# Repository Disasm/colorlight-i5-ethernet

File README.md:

# `colorlight-i5-ethernet`

Dual gigabit Ethernet interface board for [Colorlight i5 Extension Board](https://github.com/wuxx/Colorlight-FPGA-Projects). 

This board is based on [i5ether](https://github.com/kazkojima/colorlight-i5-tips/) project by
[@kazkojima](https://github.com/kazkojima).

Manufactured on JLCPCB (see `gerbers` directory). Tested with the [colorlight_i5.py example](https://github.com/litex-hub/litex-boards/blob/master/litex_boards/targets/colorlight_i5.py)
from LiteX.

# Bill of Materials

| Item                        | Part #               | LCSC Part # | Qty |
|-----------------------------|----------------------|-------------|-----|
| Connector (J1)              | X6521WR-2x15H-C30D60 | [C725927]   | 1   |
| Ethernet connector (J2, J3) | 48F-01GY2DPL2NL      | [C123172]   | 2   |
| Capacitor (C1, C2)          | GRM319R71H104KA01D   | [C86047]    | 2   |
| Capacitor (C3)              | 1812B472K202CT       | [C304036]   | 1   |

[C123172]: https://lcsc.com/product-detail/Ethernet-Connectors-Modular-Connectors-RJ45-RJ11_Shanghai-YDS-Tech-48F-01GY2DPL2NL_C123172.html
[C86047]: https://lcsc.com/product-detail/Multilayer-Ceramic-Capacitors-MLCC-SMD-SMT_Murata-Electronics-GRM319R71H104KA01D_C86047.html
[C304036]: https://lcsc.com/product-detail/Multilayer-Ceramic-Capacitors-MLCC-SMD-SMT_Walsin-Tech-Corp-1812B472K202CT_C304036.html
[C725927]: https://lcsc.com/product-detail/Pin-Headers_XKB-Connectivity-X6521WR-2x15H-C30D60_C725927.html

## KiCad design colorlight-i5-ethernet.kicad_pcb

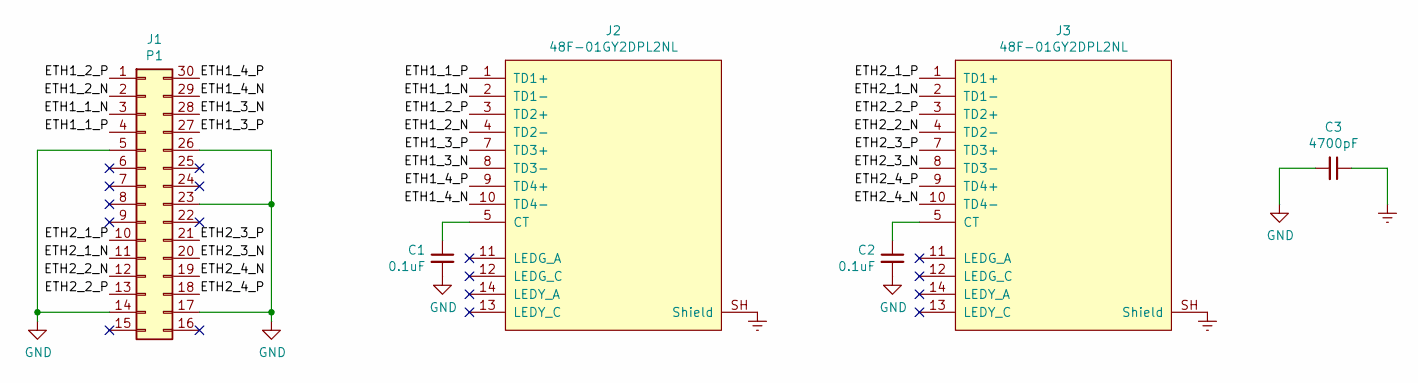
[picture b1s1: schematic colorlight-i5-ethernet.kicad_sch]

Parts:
C1, C2: 0.1uF; C_1206_3216Metric
C3: 4700pF; C_1812_4532Metric; MFR.Part # 1812B472K202CT; LCSC Part # C304036
J1: P1; PinHeader_2x15_P2.54mm_Horizontal_PMOD
J2, J3: 48F-01GY2DPL2NL; LCSC Part # C123172

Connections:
/ETH1_1_N: J1.3, J2.2 (TD1-)
/ETH1_1_P: J1.4, J2.1 (TD1+)
/ETH1_2_N: J1.2, J2.4 (TD2-)
/ETH1_2_P: J1.1, J2.3 (TD2+)
/ETH1_3_N: J1.28, J2.8 (TD3-)
/ETH1_3_P: J1.27, J2.7 (TD3+)
/ETH1_4_N: J1.29, J2.10 (TD4-)
/ETH1_4_P: J1.30, J2.9 (TD4+)
/ETH2_1_N: J1.11, J3.2 (TD1-)
/ETH2_1_P: J1.10, J3.1 (TD1+)
/ETH2_2_N: J1.12, J3.4 (TD2-)
/ETH2_2_P: J1.13, J3.3 (TD2+)
/ETH2_3_N: J1.20, J3.8 (TD3-)
/ETH2_3_P: J1.21, J3.7 (TD3+)
/ETH2_4_N: J1.19, J3.10 (TD4-)
/ETH2_4_P: J1.18, J3.9 (TD4+)
Earth: C3.1, J2.SH (Shield), J3.SH (Shield)
GND: C1.2, C2.2, C3.2, J1.5, J1.14, J1.17, J1.23, J1.26
unnamed: C1.1, J2.5 (CT), J2.6 (CT)
unnamed: C2.1, J3.5 (CT), J3.6 (CT)

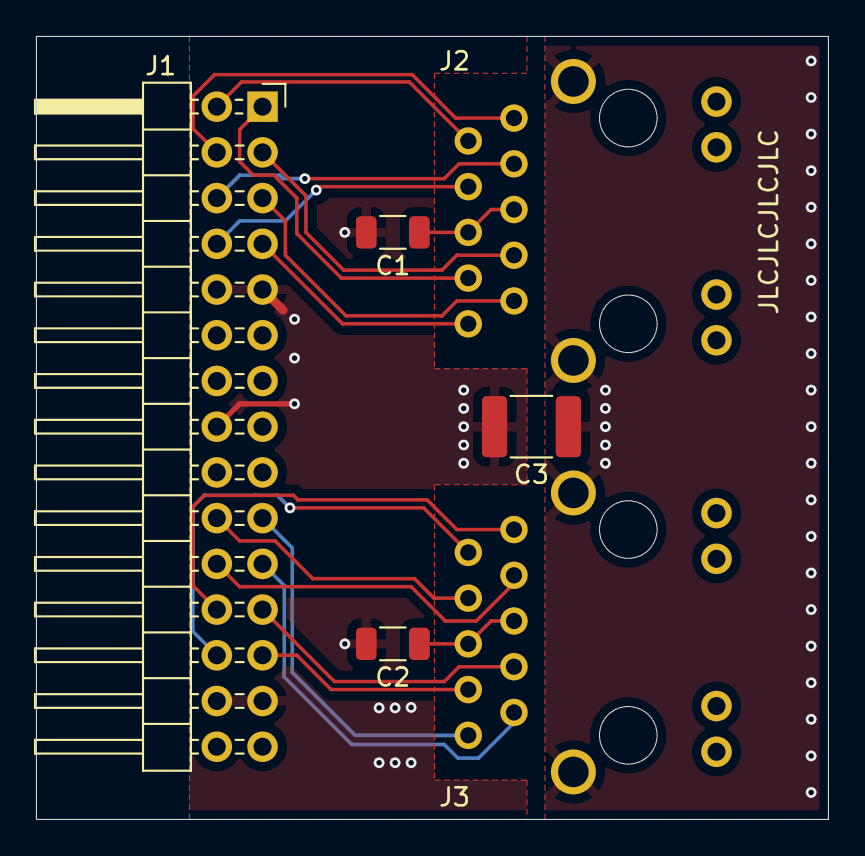
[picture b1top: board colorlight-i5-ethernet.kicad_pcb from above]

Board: 2 copper layers, 44.0 x 43.5 mm, 6 parts (0 on the bottom side), 20 nets.

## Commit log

2021-01-06 Initial version
2022-01-23 Update to KiCad 6.0, prepare for production
2022-01-23 Add gerbers
2022-02-20 Add README.md
